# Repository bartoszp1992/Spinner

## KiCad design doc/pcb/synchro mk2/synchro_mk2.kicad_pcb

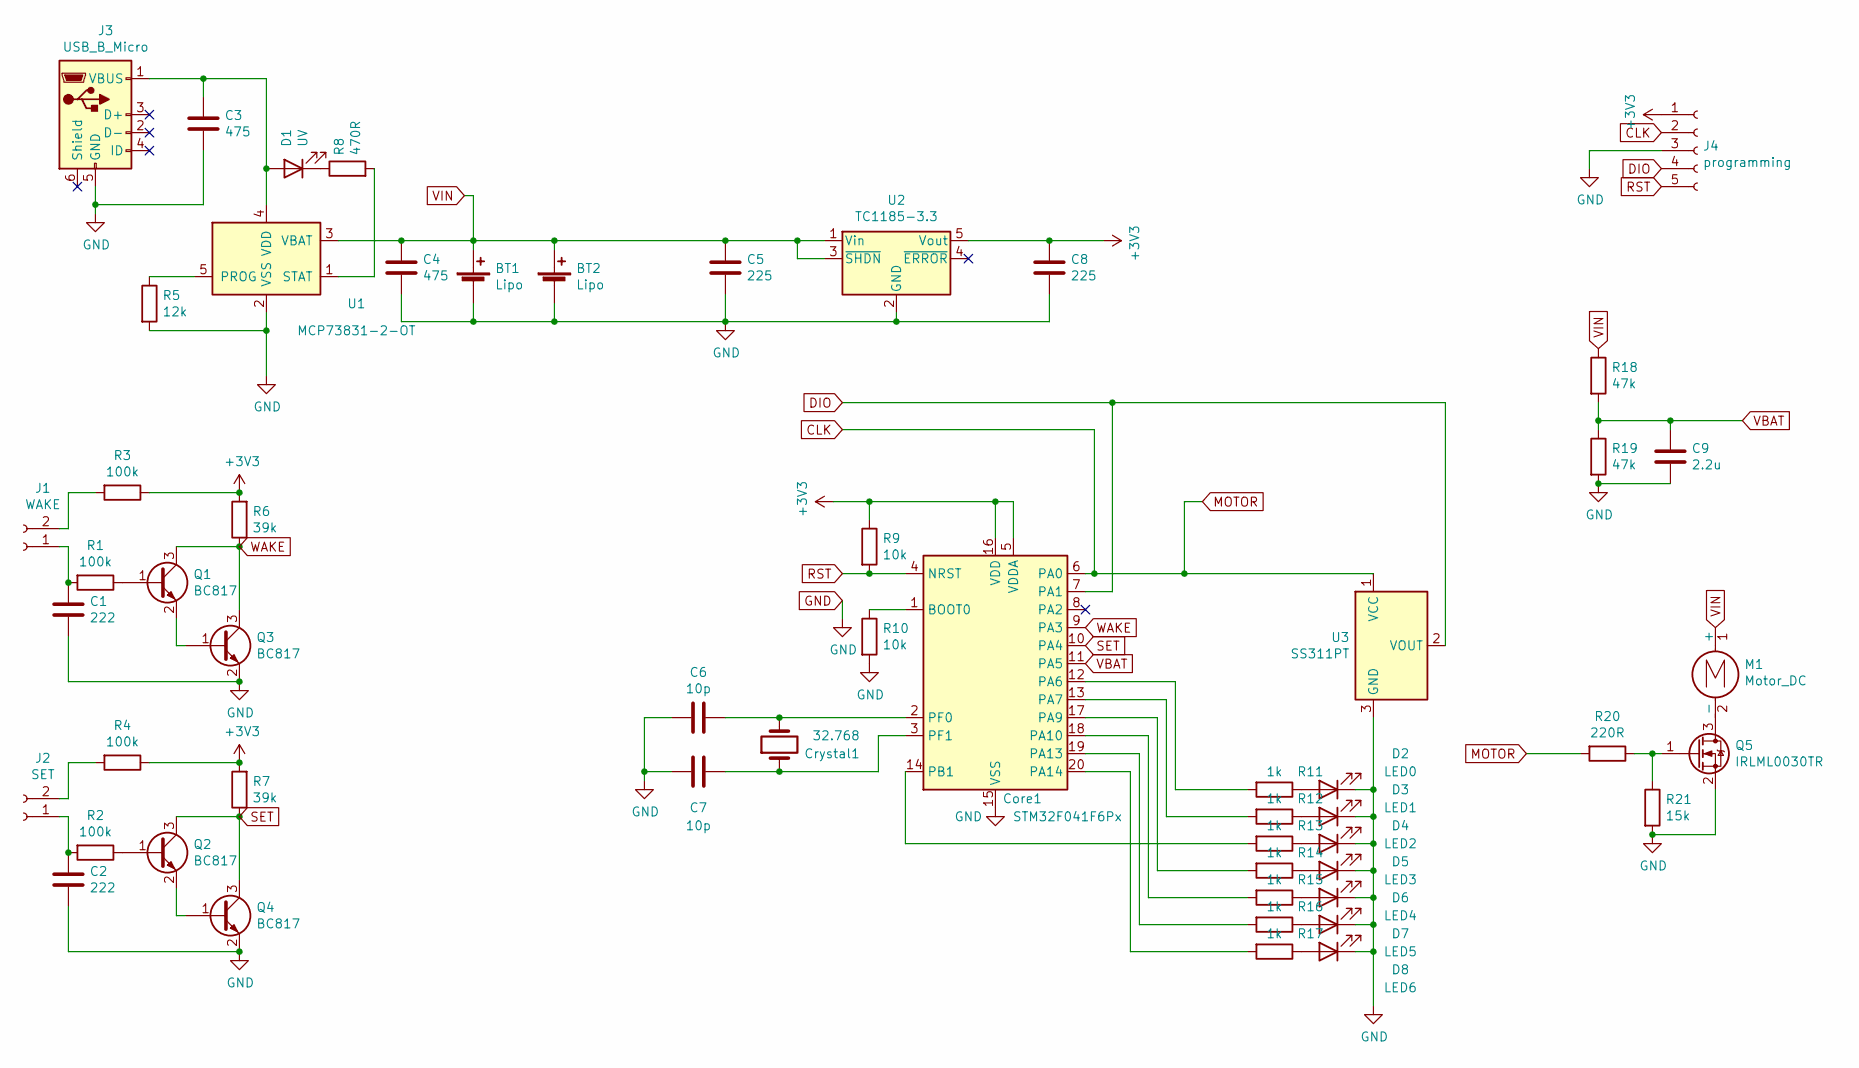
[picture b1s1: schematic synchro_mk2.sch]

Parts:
BT1, BT2: Lipo; R_2010_5025Metric
C1, C2: 222; C_0603_1608Metric
C3, C4: 475; C_0603_1608Metric
C5, C8: 225; C_0603_1608Metric
C6, C7: 10p; C_0603_1608Metric
C9: 2.2u; C_0603_1608Metric
Core1: STM32F041F6Px; TSSOP-20_4.4x6.5mm_P0.65mm
Crystal1: 32.768; Crystal_DS26_D2.0mm_L6.0mm_Horizontal
D1: UV; D_0603_1608Metric
D2: LED0; LED_0603_1608Metric
D3: LED1; LED_0603_1608Metric
D4: LED2; LED_0603_1608Metric
D5: LED3; LED_0603_1608Metric
D6: LED4; LED_0603_1608Metric
D7: LED5; LED_0603_1608Metric
D8: LED6; LED_0603_1608Metric
J1: WAKE; touchplate
J2: SET; touchplateS
J3: USB_B_Micro; USB_Micro-B_Molex_47346-0001
J4: programming; PinHeader_1x05_P1.27mm_Vertical
M1: Motor_DC; R_1206_3216Metric
Q1, Q2, Q3, Q4: BC817; SOT-23
Q5: IRLML0030TR; SOT-23
R1, R2, R3, R4: 100k; R_0603_1608Metric
R5: 12k; R_0603_1608Metric
R6, R7: 39k; R_0603_1608Metric
R8: 470R; R_0603_1608Metric
R9, R10: 10k; R_0603_1608Metric
R11, R12, R13, R14, R15, R16, R17: 1k; R_0603_1608Metric
R18, R19: 47k; R_0603_1608Metric
R20: 220R; R_0603_1608Metric
R21: 15k; R_0603_1608Metric
U1: MCP73831-2-OT; SOT-23-5
U2: TC1185-3.3; SOT-23-5
U3: SS311PT; SOT-23

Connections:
+3V3: C8.1, Core1.5 (VDDA), Core1.16 (VDD), J4.1, R3.1, R4.1, R6.2, R7.2, R9.1, U2.5 (Vout)
CLK: Core1.6 (PA0), J4.2, R20.2, U3.1 (VCC)
DIO: Core1.7 (PA1), J4.4, U3.2 (VOUT)
GND: BT1.2 (-), BT2.2 (-), C1.2, C2.2, C3.2, C4.2, C5.2, C6.2, C7.2, C8.2, C9.2, Core1.15 (VSS), D2.1 (K), D3.1 (K), D4.1 (K), D5.1 (K), D6.1 (K), D7.1 (K), D8.1 (K), J3.5 (GND), J4.3, Q3.2 (E), Q4.2 (E), Q5.2 (S), R5.2, R10.2, R19.2, R21.2, U1.2 (VSS), U2.2 (GND), U3.3 (GND)
unnamed: C1.1, J1.1, R1.2
unnamed: C2.1, J2.1, R2.2
unnamed: C3.1, D1.2 (A), J3.1 (VBUS), U1.4 (VDD)
unnamed: C6.1, Core1.2 (PF0), Crystal1.2
unnamed: C7.1, Core1.3 (PF1), Crystal1.1
unnamed: Core1.1 (BOOT0), R10.1
unnamed: Core1.12 (PA6), R11.2
unnamed: Core1.13 (PA7), R12.2
unnamed: Core1.14 (PB1), R13.2
unnamed: Core1.17 (PA9), R14.2
unnamed: Core1.18 (PA10), R15.2
unnamed: Core1.19 (PA13), R16.2
unnamed: Core1.20 (PA14), R17.2
unnamed: D1.1 (K), R8.1
unnamed: D2.2 (A), R11.1
unnamed: D3.2 (A), R12.1
unnamed: D4.2 (A), R13.1
unnamed: D5.2 (A), R14.1
unnamed: D6.2 (A), R15.1
unnamed: D7.2 (A), R16.1
unnamed: D8.2 (A), R17.1
unnamed: J1.2, R3.2
unnamed: J2.2, R4.2
unnamed: M1.2 (-), Q5.3 (D)
unnamed: Q1.1 (B), R1.1
unnamed: Q1.2 (E), Q3.1 (B)
unnamed: Q2.1 (B), R2.1
unnamed: Q2.2 (E), Q4.1 (B)
unnamed: Q5.1 (G), R20.1, R21.1
unnamed: R5.1, U1.5 (PROG)
unnamed: R8.2, U1.1 (STAT)
RST: Core1.4 (NRST), J4.5, R9.2
SET: Core1.10 (PA4), Q2.3 (C), Q4.3 (C), R7.1
VBAT: C9.1, Core1.11 (PA5), R18.2, R19.1
VIN: BT1.1 (+), BT2.1 (+), C4.1, C5.1, M1.1 (+), R18.1, U1.3 (VBAT), U2.1 (Vin), U2.3 (~SHDN)
WAKE: Core1.9 (PA3), Q1.3 (C), Q3.3 (C), R6.1

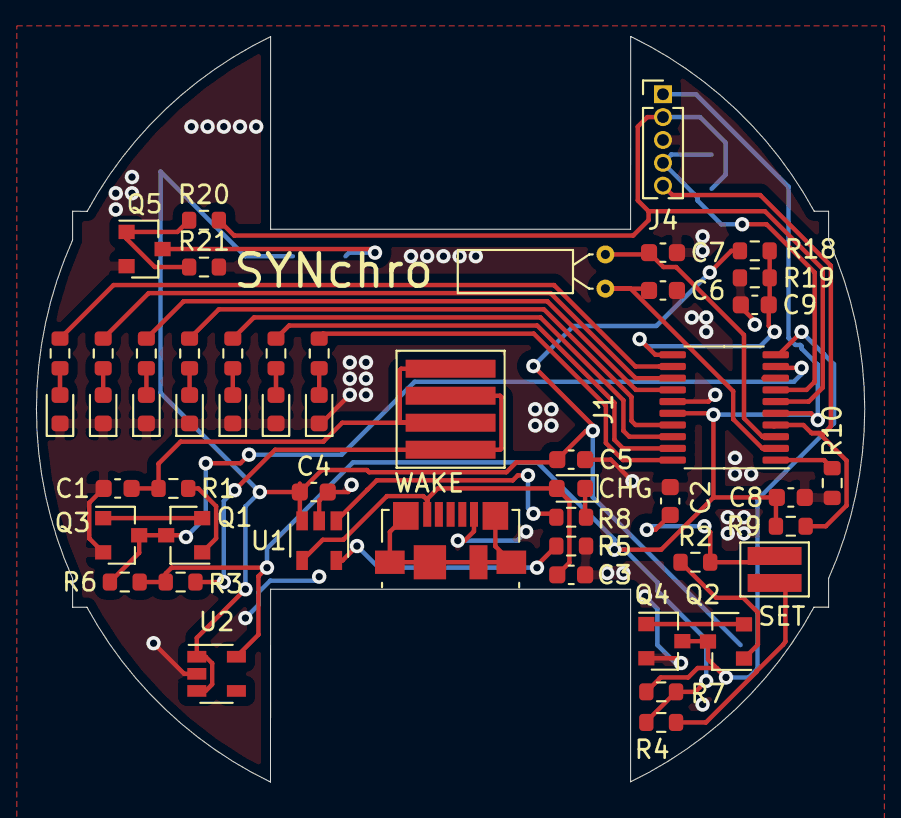
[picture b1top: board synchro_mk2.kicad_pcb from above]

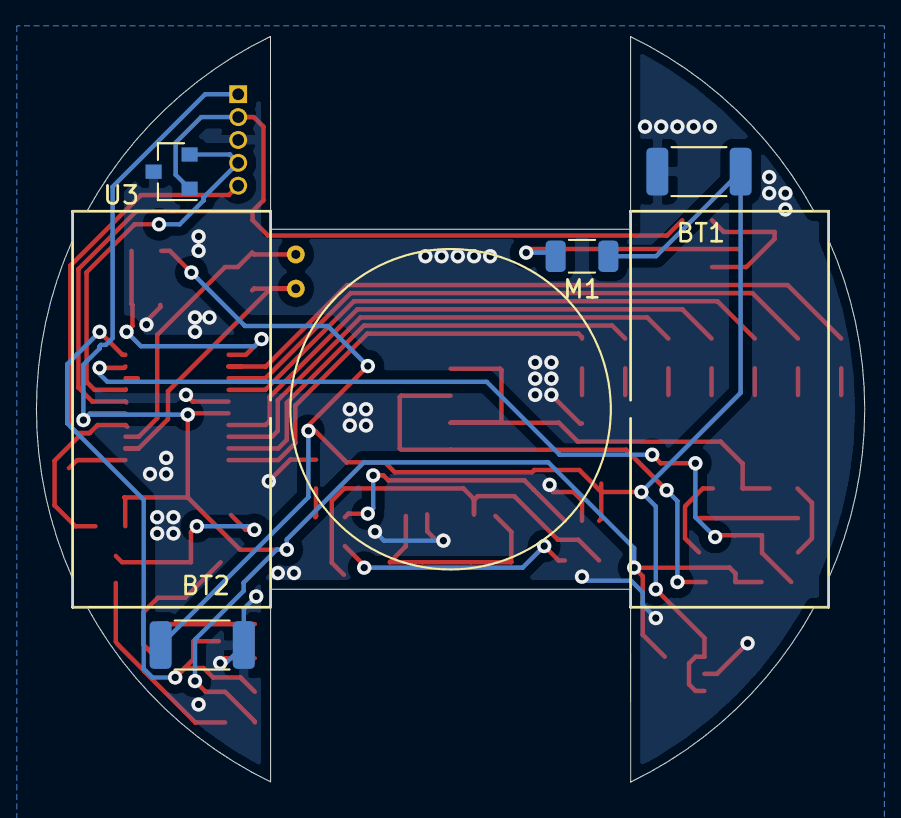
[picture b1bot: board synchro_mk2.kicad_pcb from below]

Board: 2 copper layers, 46.0 x 41.4 mm, 55 parts (4 on the bottom side), 40 nets.

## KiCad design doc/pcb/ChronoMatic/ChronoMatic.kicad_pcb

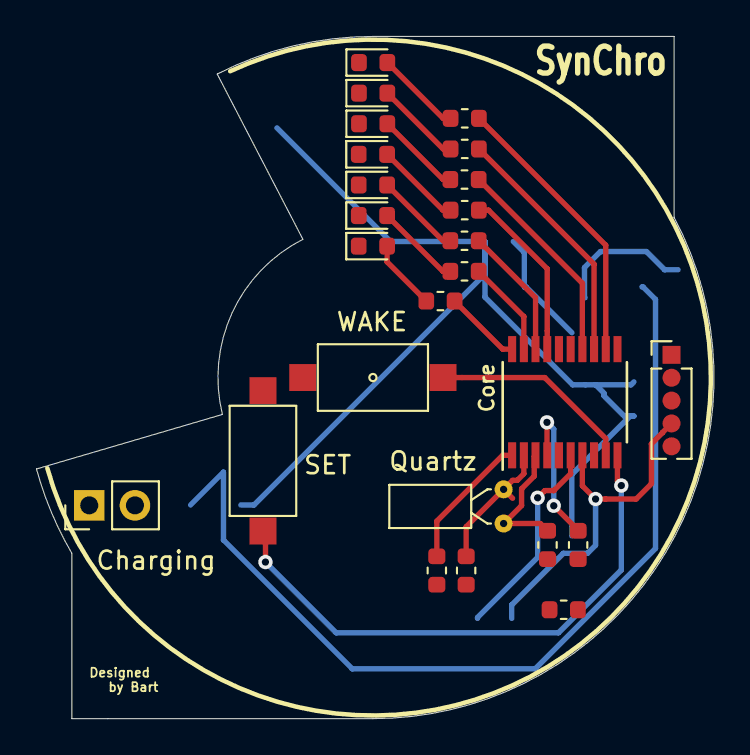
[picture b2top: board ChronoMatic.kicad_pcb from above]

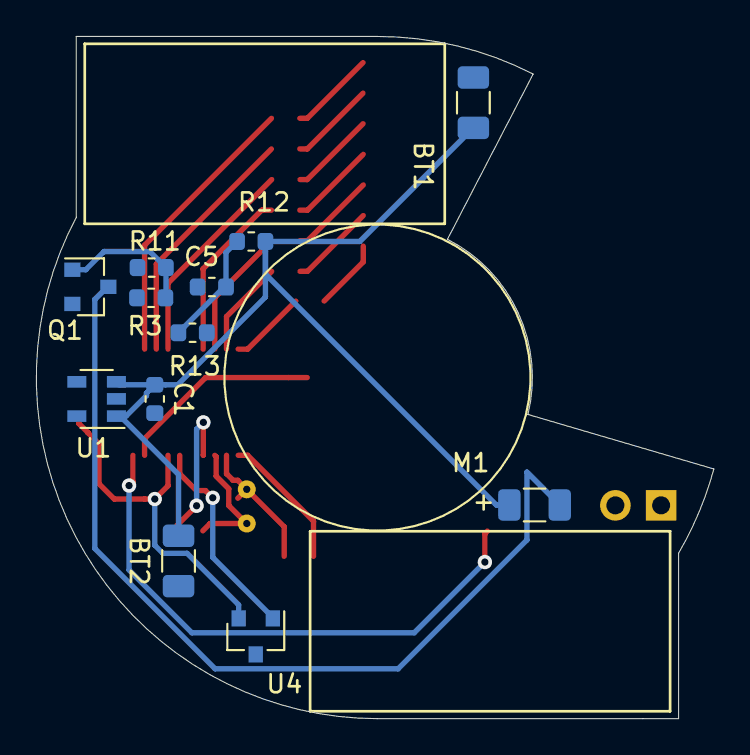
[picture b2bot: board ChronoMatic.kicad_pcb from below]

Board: 2 copper layers, 37.6 x 37.9 mm, 37 parts (12 on the bottom side), 28 nets.

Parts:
  : Conn_01x05_Female; PinHeader_1x05_P1.27mm_Vertical
BT1, BT2: Battery_Cell; R_1206_3216Metric
C1, C2: 100n; C_0603_1608Metric
C3, C4: 10p; C_0603_1608Metric
C5: 2.2u; C_0603_1608Metric
Charging: Charging port; PinHeader_1x02_P2.54mm_Vertical
Core: STM32F041F6Px; TSSOP-20_4.4x6.5mm_P0.65mm
D1: LED0; LED_0603_1608Metric
D2: LED1; LED_0603_1608Metric
D3: LED2; LED_0603_1608Metric
D4: LED3; LED_0603_1608Metric
D5: LED4; LED_0603_1608Metric
D6: LED5; LED_0603_1608Metric
D7: LED6; LED_0603_1608Metric
M1: Motor_DC; R_1206_3216Metric
Q1: IRLML0030TR; SOT-23
Quartz: 32.768; Crystal_DS26_D2.0mm_L6.0mm_Horizontal
R1, R2: 10k; R_0603_1608Metric
R3: 220R; R_0603_1608Metric
R4, R5, R6, R7, R8, R9, R10: 1k; R_0603_1608Metric
R11: 15k; R_0603_1608Metric
R12, R13: 100k; R_0603_1608Metric
SET: SET; SW_SPST_CK_RS282G05A3
U1: TC1185-3.3VCT8; SOT-23-5
U4: SS311PT; SOT-23
WAKE: WAKE; SW_SPST_CK_RS282G05A3

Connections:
+5V: BT1.1, BT2.1, C1.1, Charging.2, M1.1, R12.1, U1.1, U1.3
CLK: .2, Core.6, R3.2, U4.1
DIO: .4, Core.7, U4.2
GND: .3, BT1.2, BT2.2, C1.2, C2.2, C3.2, C4.2, C5.2, Charging.1, Core.15, D1.1, D2.1, D3.1, D4.1, D5.1, D6.1, D7.1, Q1.2, R2.2, R11.2, R13.2, SET.2, U1.2, U4.3, WAKE.2
unnamed: C3.1, Core.2, Quartz.1
unnamed: C4.1, Core.3, Quartz.2
unnamed: D1.2, R4.1
unnamed: D2.2, R5.1
unnamed: D3.2, R6.1
unnamed: D4.2, R7.1
unnamed: D5.2, R8.1
unnamed: D6.2, R9.1
unnamed: D7.2, R10.1
unnamed: M1.2, Q1.3
unnamed: Q1.1, R3.1, R11.1
unnamed: Core.1, R2.1
unnamed: Core.12, R4.2
unnamed: Core.13, R5.2
unnamed: Core.14, R6.2
unnamed: Core.17, R7.2
unnamed: Core.18, R8.2
unnamed: Core.19, R9.2
unnamed: Core.20, R10.2
unnamed: Core.9, WAKE.1
unnamed: Core.10, SET.1
RST: .5, Core.4, R1.2
VBAT: C5.1, Core.11, R12.2, R13.1
Vcc: .1, C2.1, Core.5, Core.16, R1.1, U1.5

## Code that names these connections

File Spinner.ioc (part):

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Mcu.Name=STM32L041F6Px
Mcu.Package=TSSOP20
Mcu.UserName=STM32L041F6Px
PA0-CK_IN.GPIOParameters=GPIO_Label
PA0-CK_IN.GPIO_Label=HALL
PA0-CK_IN.Signal=GPIO_Output
PA1.GPIOParameters=GPIO_PuPd,GPIO_Label,GPIO_ModeDefaultEXTI
PA1.GPIO_Label=EXTI
PA1.GPIO_ModeDefaultEXTI=GPIO_MODE_IT_RISING
PA1.GPIO_PuPd=GPIO_NOPULL
PA1.Signal=GPXTI1
PA10.GPIOParameters=GPIO_Label
PA10.GPIO_Label=L4
PA10.Signal=GPIO_Output
PA13.GPIOParameters=GPIO_Label
PA13.GPIO_Label=L5
PA13.Signal=GPIO_Output
PA14.GPIOParameters=GPIO_Label
PA14.GPIO_Label=L6
PA14.Signal=GPIO_Output
PA3.GPIOParameters=GPIO_PuPd,GPIO_Label,GPIO_ModeDefaultEXTI
PA3.GPIO_Label=WAKE
PA3.GPIO_ModeDefaultEXTI=GPIO_MODE_IT_FALLING
PA3.GPIO_PuPd=GPIO_PULLUP
PA3.Signal=GPXTI3
PA4.GPIOParameters=GPIO_PuPd,GPIO_Label,GPIO_ModeDefaultEXTI
PA4.GPIO_Label=SET
PA4.GPIO_ModeDefaultEXTI=GPIO_MODE_IT_FALLING
PA4.GPIO_PuPd=GPIO_PULLUP
PA4.Signal=GPXTI4
PA5.GPIOParameters=GPIO_Label
PA5.GPIO_Label=VBAT
PA5.Mode=IN5
PA5.Signal=ADC_IN5
PA6.GPIOParameters=GPIO_Label
PA6.GPIO_Label=L0
PA6.Signal=GPIO_Output
PA7.GPIOParameters=GPIO_Label
PA7.GPIO_Label=L1
PA7.Signal=GPIO_Output
PA9.GPIOParameters=GPIO_Label
PA9.GPIO_Label=L3
PA9.Signal=GPIO_Output
PB1.GPIOParameters=GPIO_Label
PB1.GPIO_Label=L2
PB1.Signal=GPIO_Output
PC14-OSC32_IN.Mode=LSE-External-Oscillator
PC14-OSC32_IN.Signal=RCC_OSC32_IN
PC15-OSC32_OUT.Mode=LSE-External-Oscillator
PC15-OSC32_OUT.Signal=RCC_OSC32_OUT
RCC.HSE_VALUE=8000000
RCC.SYSCLKFreq_VALUE=32000000
RCC.SYSCLKSource=RCC_SYSCLKSOURCE_PLLCLK
board=custom

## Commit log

2019-09-11 fixed freeze in the sun
2019-09-13 shorted working time to 20s
2019-09-20 hall sensor, updated scheme and pcb
2019-09-21 new pcb
2019-09-21 added ring, corrected counterclockwise mode
2019-09-22 added new version of matrixDisplay, better RING(PCB)
2019-09-22 added connections for ADC
2019-09-22 v0.71
2019-09-23 trying to make it working
2019-09-23 priorities
2019-09-23 again old file
2019-09-27 added cage pcb
2019-09-27 v0.73
2019-09-30 added adc version
2019-09-30 adc initial
2019-09-30 adc stucks
2019-09-30 v0.8
2019-09-30 corrected weaktime
2019-10-04 v0.4 pcb
2019-10-04 +gerber files
2019-10-09 BOM update
2019-10-11 added base, correct stabiliser name
2019-10-21 firmware v1.0
2019-10-21 little corrections
2019-10-23 new times
2019-10-23 v1.1
2019-10-24 v1.2
2019-10-31 exported clock base
2019-10-31 small tree changes
2019-11-05 mechanical corrections
2019-11-05 testowy update
2019-11-11 bom updated with cells model
2019-11-18 dunno
2019-12-10 documentation
2019-12-23 small corrections
2019-12-25 case initial
2019-12-29 added case
2020-01-04 separate folder for 1st verison case
2020-04-10 included datasheets for mcu
2020-05-23 new v3 case
2020-05-24 new case
2020-05-26 dxfs
2020-05-29 dxf export
2020-07-29 new design
2020-10-18 small pcb corrections
2021-09-27 new board
